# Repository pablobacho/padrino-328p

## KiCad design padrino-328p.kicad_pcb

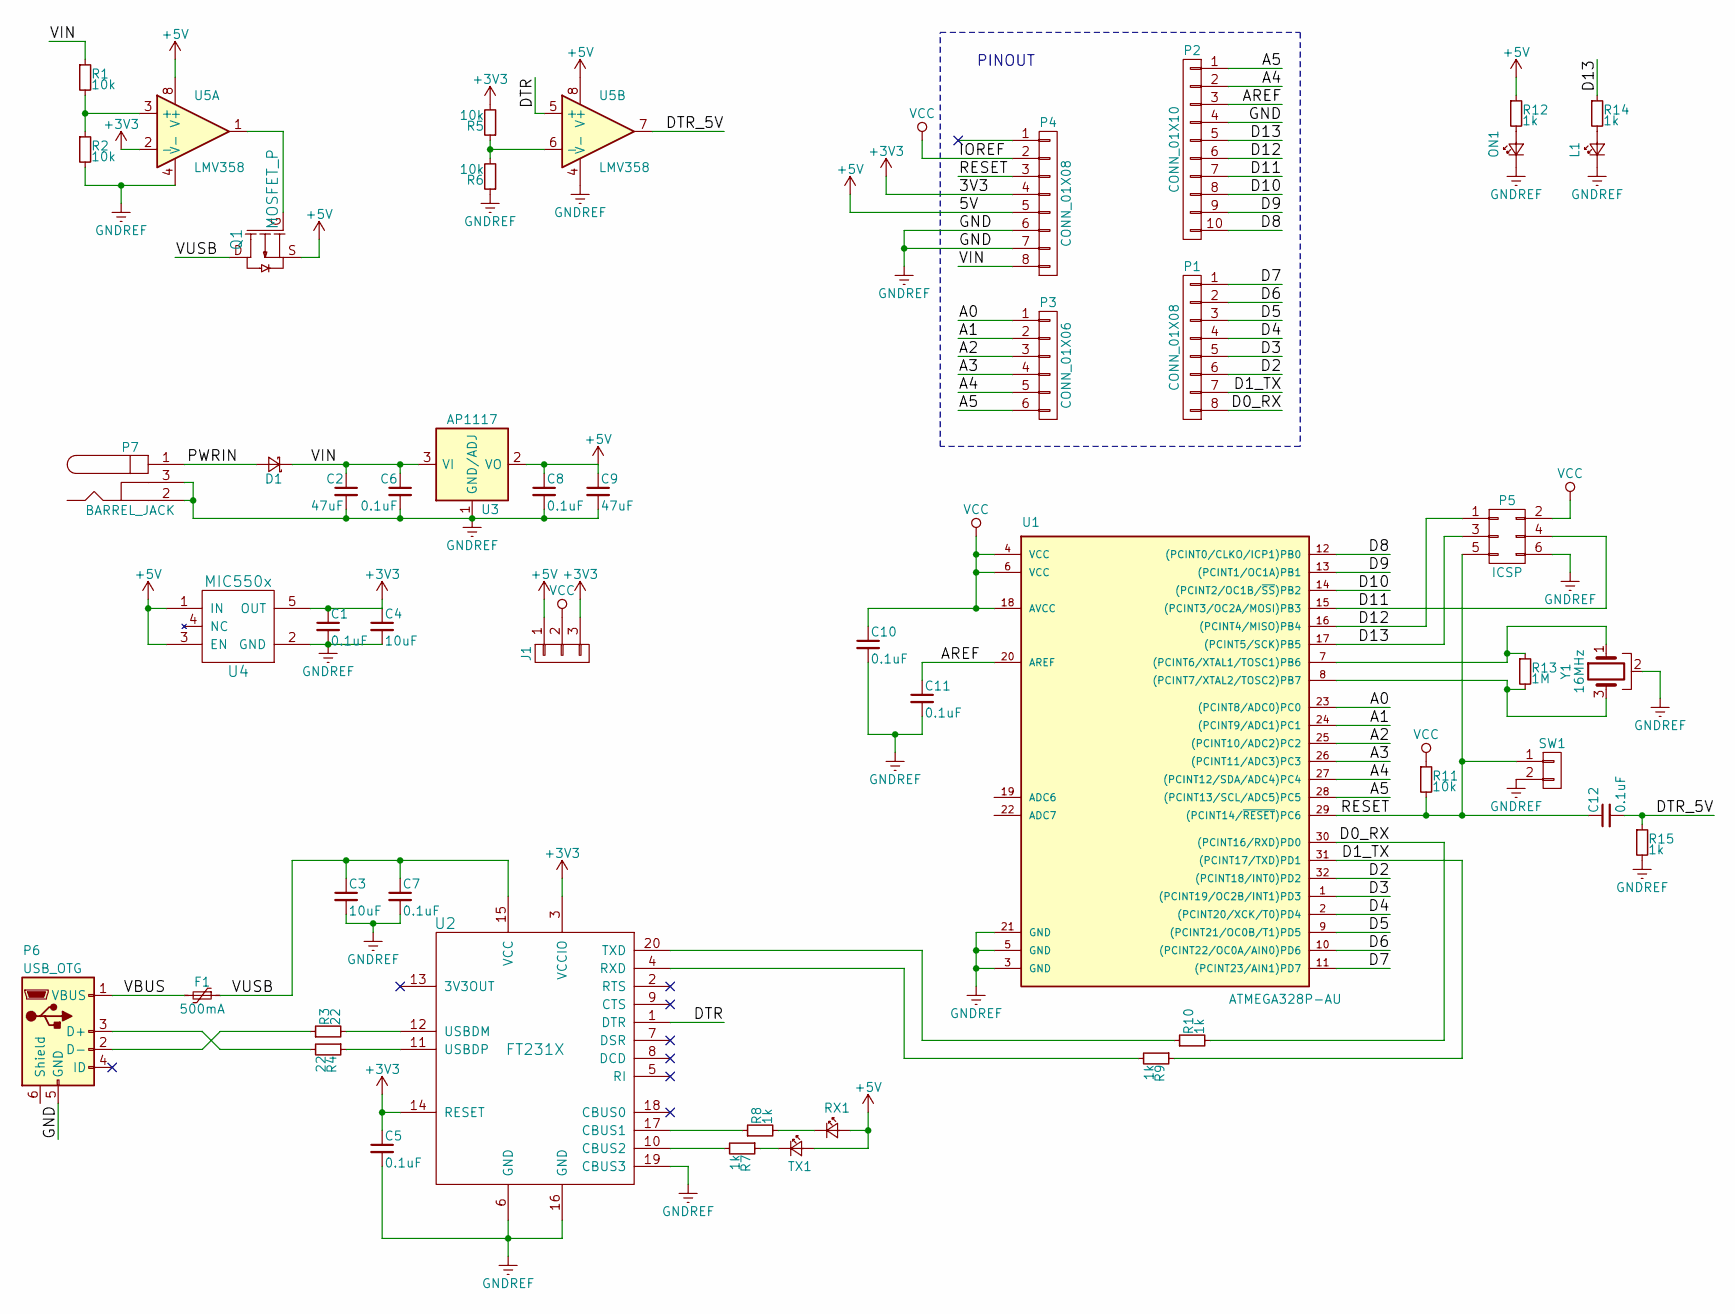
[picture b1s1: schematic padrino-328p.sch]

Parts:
C1, C5, C6, C7, C8, C10, C11, C12: 0.1uF; C_0603
C2, C9: 47uF; UWT_63x58
C3, C4: 10uF; C_1206
D1: D_Schottky_Small; SS24FL
F1: 500mA; R_1812
J1: CONN_01X03; solderable_jumper_3
L1: LED_Small; LED_0805
ON1: LED_Small; LED_0805
P1, P4: CONN_01X08; sneaky_header_01x08_str_2.54mm
P2: CONN_01X10; sneaky_header_01x10_str_2.54mm
P3: CONN_01X06; sneaky_header_01x06_str_2.54mm
P5: ICSP; Pin_Header_Straight_2x03_Pitch2.54mm
P6: USB_OTG; 10118192-0001LF
P7: BARREL_JACK; CUI_PJxxx_ROUND
Q1: MOSFET_P; DMP3099L
R1, R2, R5, R6, R11: 10k; R_0603
R3, R4: 22; R_0603
R7, R8, R9, R10, R12, R14, R15: 1k; R_0603
R13: 1M; R_0603
RX1: LED_Small; LED_0805
SW1: CONN_01X02; 1825027
TX1: LED_Small; LED_0805
U1: ATMEGA328P-AU; TQFP-32_7x7mm_Pitch0.8mm
U2: FT231X; FT231XS
U3: AP1117; NCP1117LP_SOT-223
U4: MIC550x; MIC550X_SOT-23
U5: LMV358; LMV358LIPT
Y1: 16MHz; CSTCE_V

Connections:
+3V3: C1.1, C4.1, C5.1, J1.3, P4.4, R5.2, U2.3 (VCCIO), U2.14 (RESET), U4.5 (OUT), U5.2 (-)
+5V: C8.1, C9.1, J1.1, P4.5, Q1.S, R12.1, RX1.2 (A), TX1.2 (A), U3.2 (VO), U3.4 (VO), U4.1 (IN), U4.3 (EN), U5.8 (V+); also elsewhere on the board
/A0: P3.1, U1.23 ((PCINT8/ADC0)PC0)
/A1: P3.2, U1.24 ((PCINT9/ADC1)PC1)
/A2: P3.3, U1.25 ((PCINT10/ADC2)PC2)
/A3: P3.4, U1.26 ((PCINT11/ADC3)PC3)
/A4: P2.2, P3.5, U1.27 ((PCINT12/SDA/ADC4)PC4)
/A5: P2.1, P3.6, U1.28 ((PCINT13/SCL/ADC5)PC5)
/AREF: C11.1, P2.3, U1.20 (AREF)
/D0_RX: P1.8, R10.2, U1.30 ((PCINT16/RXD)PD0)
/D1_TX: P1.7, R9.1, U1.31 ((PCINT17/TXD)PD1)
/D2: P1.6, U1.32 ((PCINT18/INT0)PD2)
/D3: P1.5, U1.1 ((PCINT19/OC2B/INT1)PD3)
/D4: P1.4, U1.2 ((PCINT20/XCK/T0)PD4)
/D5: P1.3, U1.9 ((PCINT21/OC0B/T1)PD5)
/D6: P1.2, U1.10 ((PCINT22/OC0A/AIN0)PD6)
/D7: P1.1, U1.11 ((PCINT23/AIN1)PD7)
/D8: P2.10, U1.12 ((PCINT0/CLKO/ICP1)PB0)
/D9: P2.9, U1.13 ((PCINT1/OC1A)PB1)
/D10: P2.8, U1.14 ((PCINT2/OC1B/~SS~)PB2)
/D11: P2.7, P5.4, U1.15 ((PCINT3/OC2A/MOSI)PB3)
/D12: P2.6, P5.1, U1.16 ((PCINT4/MISO)PB4)
/D13: P2.5, P5.3, R14.1, U1.17 ((PCINT5/SCK)PB5)
/DTR: U2.1 (DTR), U5.5 (+)
/DTR_5V: C12.2, R15.1, U5.7
/PWRIN: D1.2 (A), P7.1
/RESET: C12.1, P4.3, P5.5, R11.2, SW1.1, U1.29 ((PCINT14/~RESET~)PC6)
/VBUS: F1.2, P6.1 (VBUS)
/VIN: C2.1, C6.1, D1.1 (K), P4.8, R1.1, U3.3 (VI)
/VUSB: C3.1, C7.1, F1.1, Q1.D, U2.15 (VCC)
GNDREF: C1.2, C2.2, C3.2, C4.2, C5.2, C6.2, C7.2, C8.2, C9.2, C10.2, C11.2, L1.1 (K), ON1.1 (K), P2.4, P4.6, P4.7, P5.6, P6.5 (GND), P7.2, P7.3, R2.2, R6.1, R15.2, SW1.2, U1.3 (GND), U1.5 (GND), U1.21 (GND), U2.6 (GND), U2.16 (GND), U2.19 (CBUS3), U3.1 (GND/ADJ), U4.2 (GND), U5.4 (V-), Y1.2; also elsewhere on the board
unnamed 31: L1.2 (A), R14.2; also elsewhere on the board
unnamed 32: ON1.2 (A), R12.2; also elsewhere on the board
unnamed: P6.2 (D-), R3.1
unnamed: P6.3 (D+), R4.2
unnamed: Q1.G, U5.1
unnamed: R1.2, R2.1, U5.3 (+)
unnamed: R3.2, U2.12 (USBDM)
unnamed: R4.1, U2.11 (USBDP)
unnamed: R5.1, R6.2, U5.6 (-)
unnamed 43: R7.1, TX1.1 (K); also elsewhere on the board
unnamed: R7.2, U2.10 (CBUS2)
unnamed: R8.1, U2.17 (CBUS1)
unnamed 46: R8.2, RX1.1 (K); also elsewhere on the board
unnamed: R9.2, U2.4 (RXD)
unnamed: R10.1, U2.20 (TXD)
unnamed: R13.1, U1.7 ((PCINT6/XTAL1/TOSC1)PB6), Y1.1
unnamed: R13.2, U1.8 ((PCINT7/XTAL2/TOSC2)PB7), Y1.3
VCC: C10.1, J1.2, P4.2, P5.2, R11.1, U1.4 (VCC), U1.6 (VCC), U1.18 (AVCC)

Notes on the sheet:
PINOUT

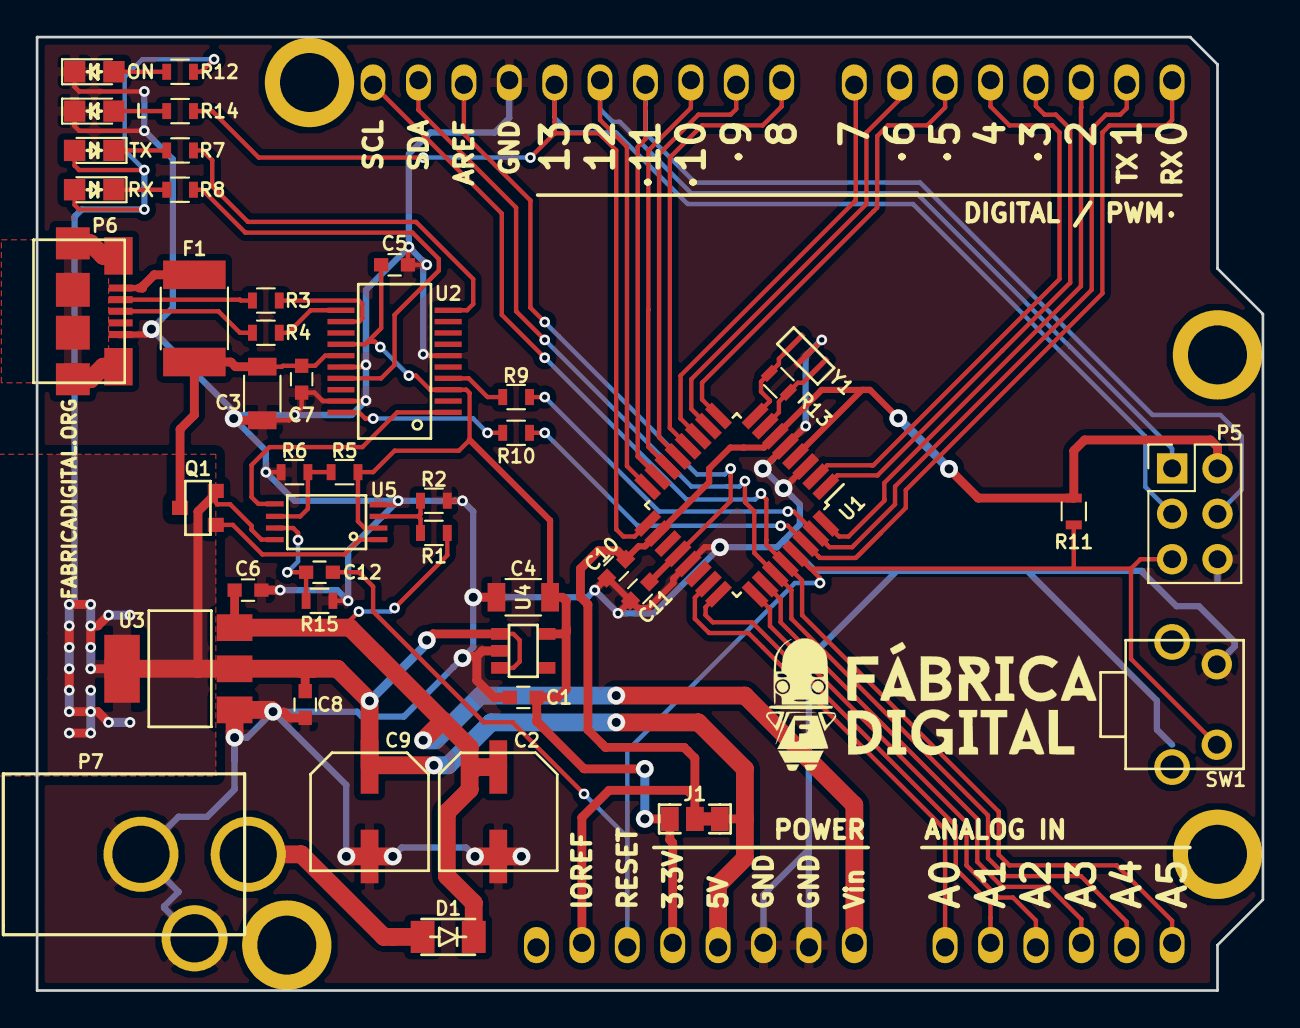
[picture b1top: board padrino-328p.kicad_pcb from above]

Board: 2 copper layers, 68.6 x 53.3 mm, 49 parts (0 on the bottom side), 49 nets.

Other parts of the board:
L: LED_Small; LED_0805
ON: LED_Small; LED_0805
RX: LED_Small; LED_0805
TX: LED_Small; LED_0805

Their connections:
+5V: RX.2, TX.2; also elsewhere on the board
GNDREF: L.1, ON.1; also elsewhere on the board
unnamed 31: L.2; also elsewhere on the board
unnamed 32: ON.2; also elsewhere on the board
unnamed 43: TX.1; also elsewhere on the board
unnamed 46: RX.1; also elsewhere on the board

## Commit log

2018-03-06 Arregladas orientación del botón de reset y pinout del regulador de 3.3V
